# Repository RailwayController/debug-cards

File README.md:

<!--
SPDX-FileCopyrightText: 2022 Sidings Media <contact@sidingsmedia.com>
SPDX-License-Identifier: CC-BY-SA-4.0
-->

# Railway Controller - Debug boards

Boards for use with development and debugging of the system

## Licence
This repo uses the [REUSE](https://reuse.software) standard in order to
communicate the correct licence for the file. For those unfamiliar with
the standard the licence for each file can be found in one of three
places. The licence will either be in a comment block at the top of the
file, in a `.license` file with the same name as the file, or in the
dep5 file located in the `.reuse` directory. If you are unsure of the
licencing terms please contact
[contact@sidingsmedia.com](mailto:contact@sidingsmedia.com?subject=Railway%20Controller%20Licence).
All files committed to this repo must contain valid licencing
information or the pull request can not be accepted.

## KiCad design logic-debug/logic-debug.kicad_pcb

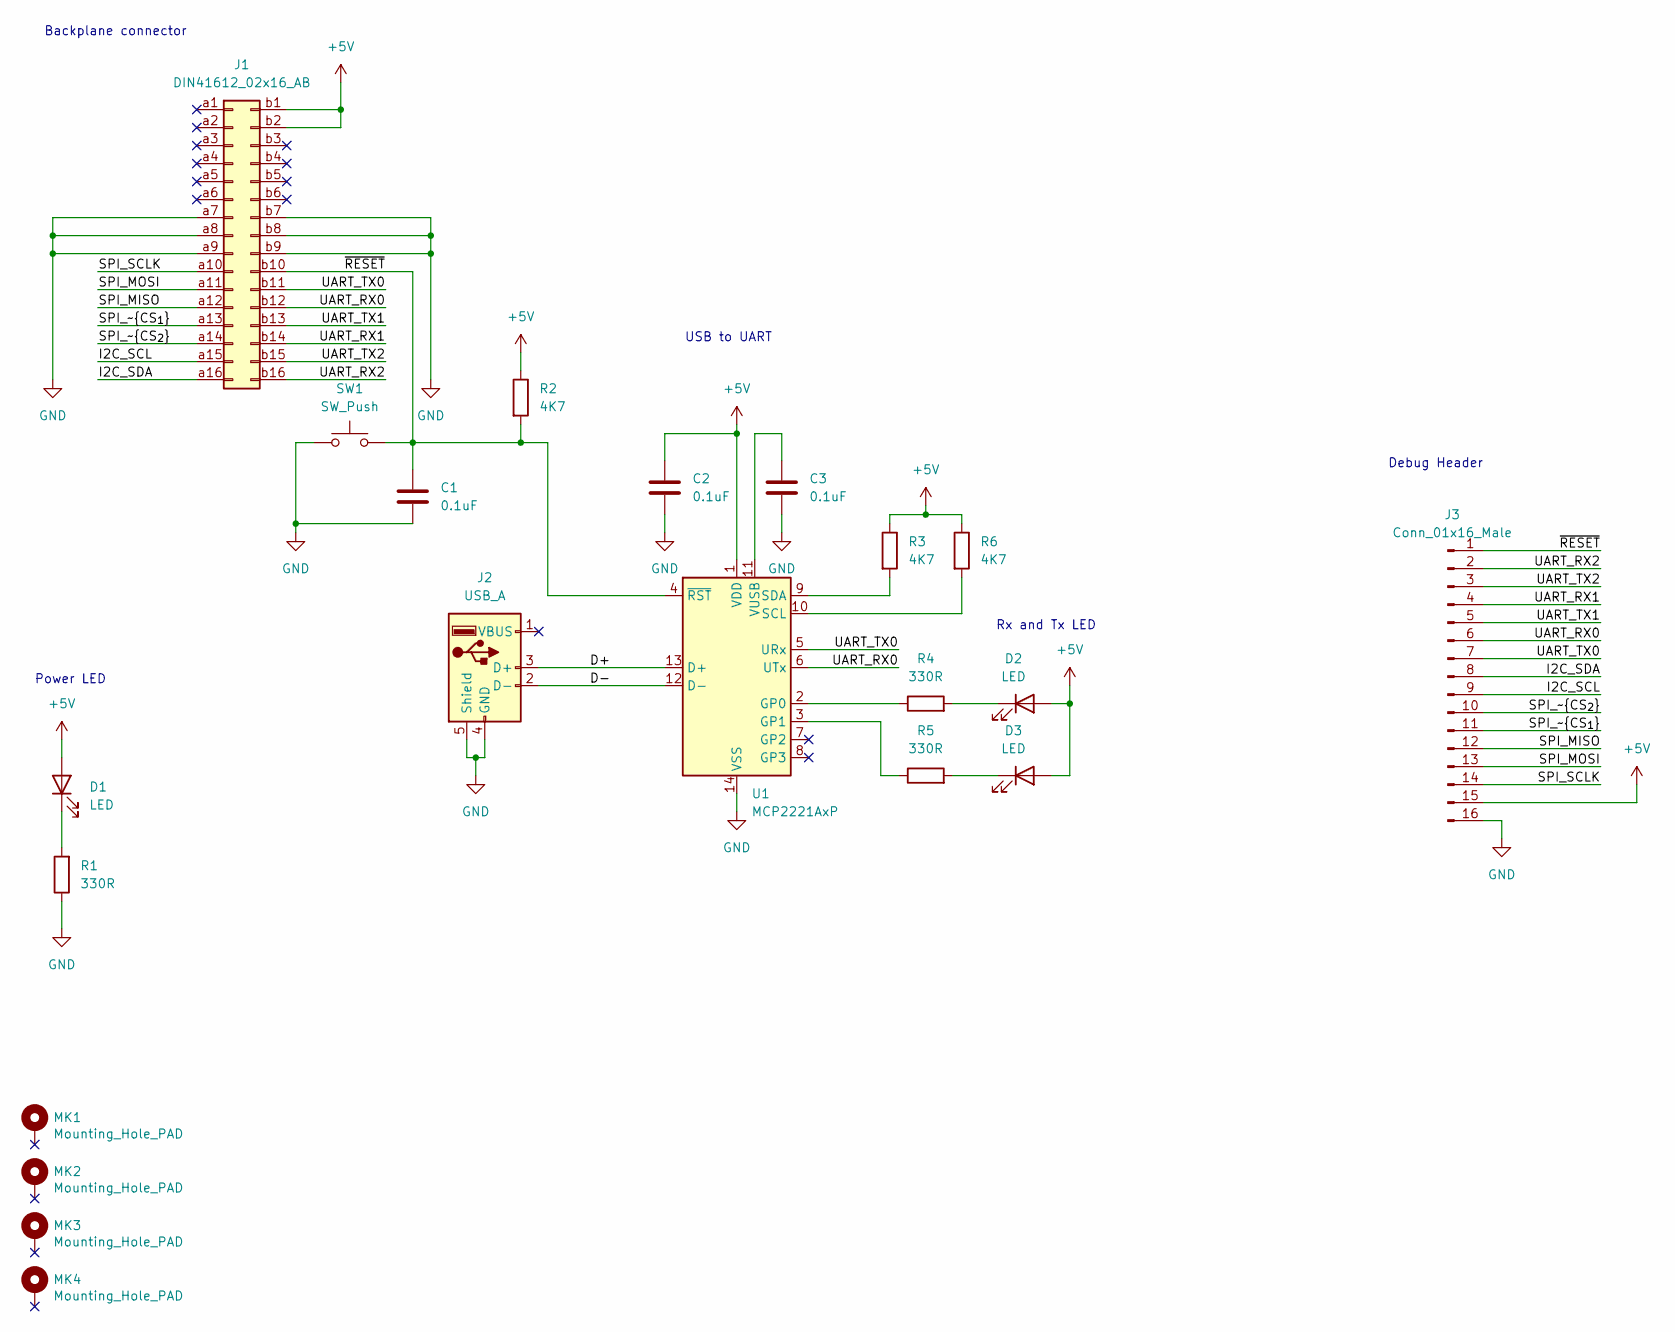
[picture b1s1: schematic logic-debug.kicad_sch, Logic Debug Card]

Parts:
C1, C2, C3: 0.1uF; C_Disc_D4.7mm_W2.5mm_P5.00mm
D1, D2, D3: LED; LED_D3.0mm
J1: DIN41612_02x16_AB; DIN41612_B2_2x16_Male_Horizontal_THT
J2: USB_A
J3: Conn_01x16_Male; PinHeader_1x16_P2.54mm_Horizontal
MK1, MK2, MK3, MK4: Mounting_Hole_PAD; MountingHole_2.7mm
R1, R4, R5: 330R; R_Axial_DIN0207_L6.3mm_D2.5mm_P7.62mm_Horizontal
R2, R3, R6: 4K7; R_Axial_DIN0207_L6.3mm_D2.5mm_P7.62mm_Horizontal
SW1: SW_Push; SW_Tactile_SPST_Angled_PTS645Vx83-2LFS
U1: MCP2221AxP; DIP-14_W7.62mm

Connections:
+5V: C2.1, D1.2 (A), D2.2 (A), D3.2 (A), J1.b1, J1.b2, J3.15, R2.1, R3.1, R6.1, U1.1 (VDD)
/D+: J2.3 (D+), U1.13 (D+)
/D-: J2.2 (D-), U1.12 (D-)
/I2C_SCL: J1.a15, J3.9
/I2C_SDA: J1.a16, J3.8
/SPI_MISO: J1.a12, J3.12
/SPI_MOSI: J1.a11, J3.13
/SPI_SCLK: J1.a10, J3.14
/SPI_~CS_{1}: J1.a13, J3.11
/SPI_~CS_{2}: J1.a14, J3.10
/UART_RX0: J1.b12, J3.6, U1.6 (UTx)
/UART_RX1: J1.b14, J3.4
/UART_RX2: J1.b16, J3.2
/UART_TX0: J1.b11, J3.7, U1.5 (URx)
/UART_TX1: J1.b13, J3.5
/UART_TX2: J1.b15, J3.3
/~RESET: C1.1, J1.b10, J3.1, R2.2, SW1.2, U1.4 (~RST)
GND: C1.2, C2.2, C3.2, J1.a7, J1.a8, J1.a9, J1.b7, J1.b8, J1.b9, J2.4 (GND), J2.5 (Shield), J3.16, R1.1, SW1.1, U1.14 (VSS)
unnamed: C3.1, U1.11 (VUSB)
unnamed: D1.1 (K), R1.2
unnamed: D2.1 (K), R4.2
unnamed: D3.1 (K), R5.2
unnamed: R3.2, U1.9 (SDA)
unnamed: R4.1, U1.2 (GP0)
unnamed: R5.1, U1.3 (GP1)
unnamed: R6.2, U1.10 (SCL)

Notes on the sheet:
Rx and Tx LED
Debug Header
Power LED
Backplane connector
USB to UART

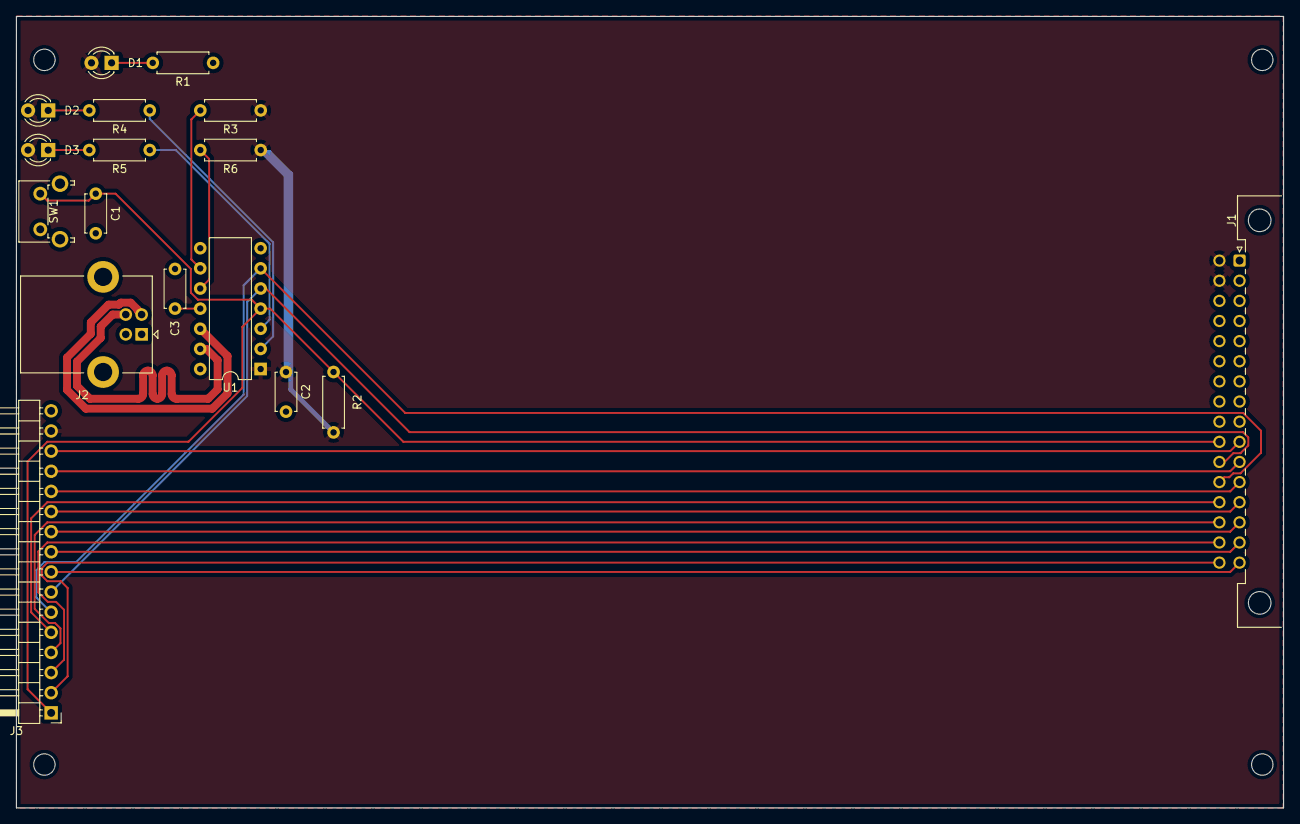
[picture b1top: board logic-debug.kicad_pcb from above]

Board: 2 copper layers, 159.9 x 99.9 mm, 21 parts (0 on the bottom side), 26 nets.

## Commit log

2022-09-17 Project initialization
2022-09-17 Added rev 0.1 of logic debug
2022-09-17 Added PDF of schematic and interactive BOM

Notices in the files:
logic-debug/logic-debug.kicad_pcb:
Licence: CERN-OHL-P-2.0 or any later version
